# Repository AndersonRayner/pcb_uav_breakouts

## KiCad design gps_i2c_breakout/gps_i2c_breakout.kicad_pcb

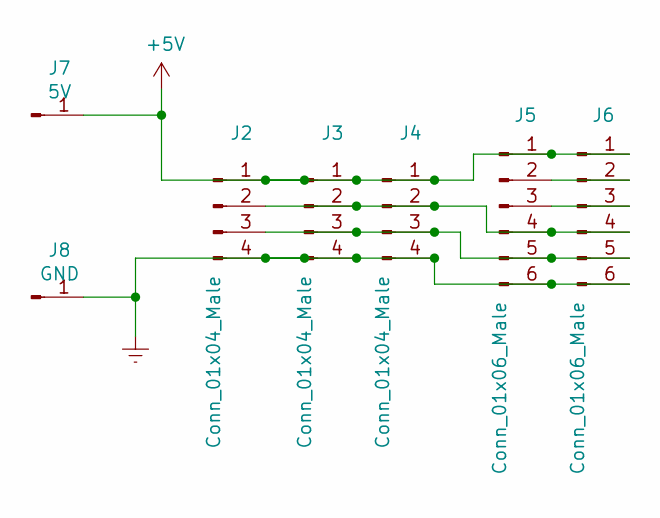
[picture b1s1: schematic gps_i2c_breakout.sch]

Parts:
J2, J3, J4: Conn_01x04_Male; JST_GH_BM04B-GHS-TBT_1x04-1MP_P1.25mm_Vertical
J5, J6: Conn_01x06_Male; JST_GH_BM06B-GHS-TBT_1x06-1MP_P1.25mm_Vertical
J7: 5V; TestPoint_Pad_2.5x2.5mm
J8: GND; TestPoint_Pad_2.5x2.5mm

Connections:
+5V: J2.1, J3.1, J4.1, J5.1, J6.1, J7.1
Earth: J2.4, J3.4, J4.4, J5.6, J6.6, J8.1
unnamed: J2.2, J3.2, J4.2, J5.4, J6.4
unnamed: J2.3, J3.3, J4.3, J5.5, J6.5
unnamed: J5.2, J6.2
unnamed: J5.3, J6.3

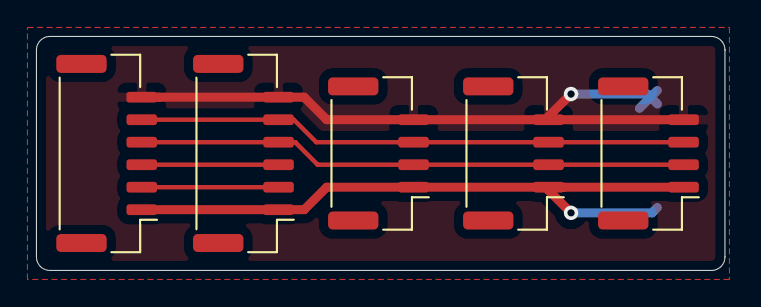
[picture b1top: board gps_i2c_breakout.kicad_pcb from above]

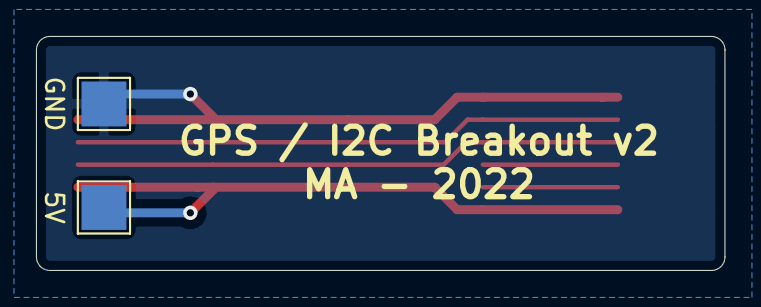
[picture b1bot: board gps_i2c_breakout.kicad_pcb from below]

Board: 2 copper layers, 38.2 x 13.0 mm, 7 parts (2 on the bottom side), 6 nets.

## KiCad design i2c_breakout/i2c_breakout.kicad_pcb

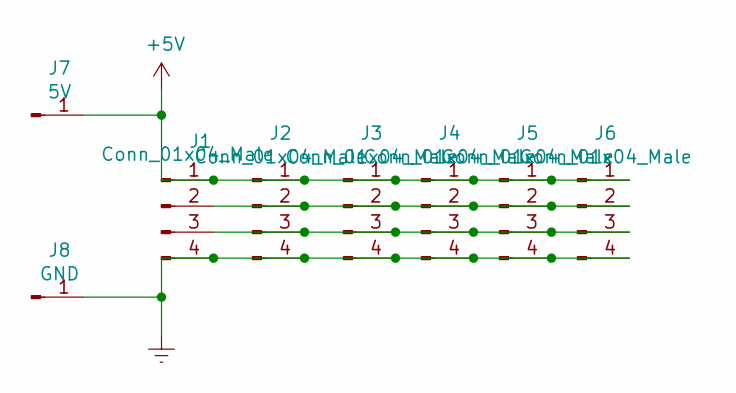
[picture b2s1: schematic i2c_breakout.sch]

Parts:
J1, J2, J3, J4, J5, J6: Conn_01x04_Male; JST_GH_BM04B-GHS-TBT_1x04-1MP_P1.25mm_Vertical
J7: 5V; TestPoint_Pad_2.5x2.5mm
J8: GND; TestPoint_Pad_2.5x2.5mm

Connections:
+5V: J1.1, J2.1, J3.1, J4.1, J5.1, J6.1, J7.1
Earth: J1.4, J2.4, J3.4, J4.4, J5.4, J6.4, J8.1
unnamed: J1.2, J2.2, J3.2, J4.2, J5.2, J6.2
unnamed: J1.3, J2.3, J3.3, J4.3, J5.3, J6.3

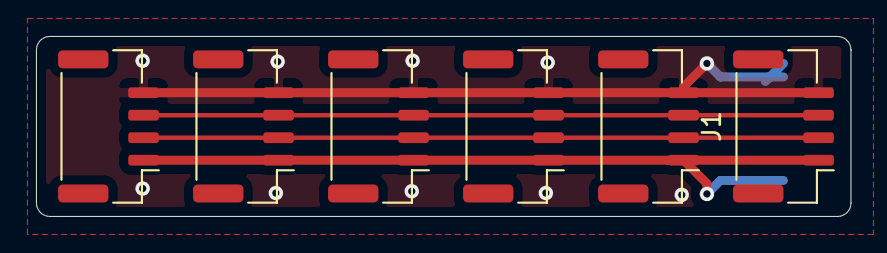
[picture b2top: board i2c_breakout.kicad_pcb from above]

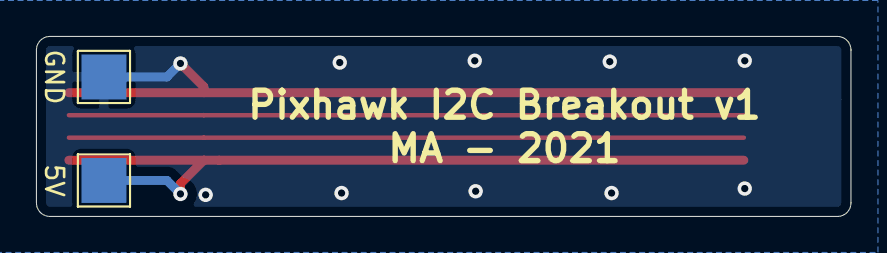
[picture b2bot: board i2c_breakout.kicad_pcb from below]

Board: 2 copper layers, 45.2 x 10.0 mm, 8 parts (2 on the bottom side), 4 nets.

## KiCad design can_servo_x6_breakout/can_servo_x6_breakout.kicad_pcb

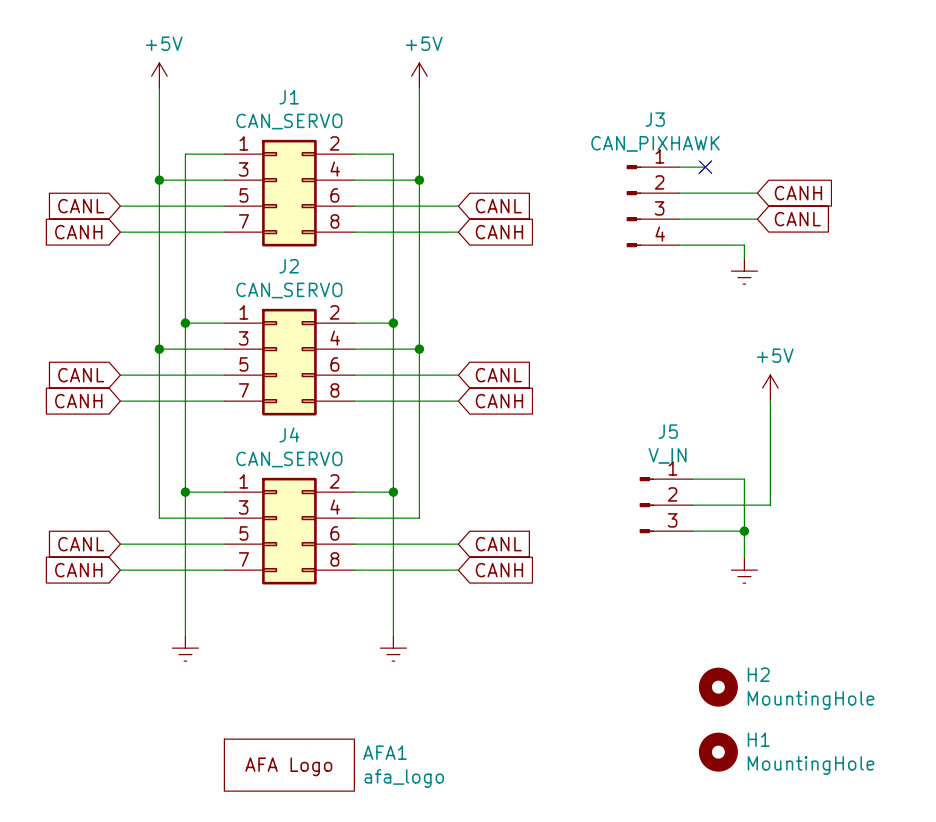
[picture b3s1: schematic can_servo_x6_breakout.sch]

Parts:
AFA1: afa_logo
H1, H2: MountingHole; MountingHole_3.2mm_M3
J1, J2, J4: CAN_SERVO; PinHeader_2x04_P2.54mm_Horizontal
J3: CAN_PIXHAWK; JST_GH_SM04B-GHS-TB_1x04-1MP_P1.25mm_Horizontal
J5: V_IN; PinHeader_1x03_P2.54mm_Horizontal

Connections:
+5V: J1.3, J1.4, J2.3, J2.4, J4.3, J4.4, J5.2
CANH: J1.7, J1.8, J2.7, J2.8, J3.2, J4.7, J4.8
CANL: J1.5, J1.6, J2.5, J2.6, J3.3, J4.5, J4.6
Earth: J1.1, J1.2, J2.1, J2.2, J3.4, J4.1, J4.2, J5.1, J5.3

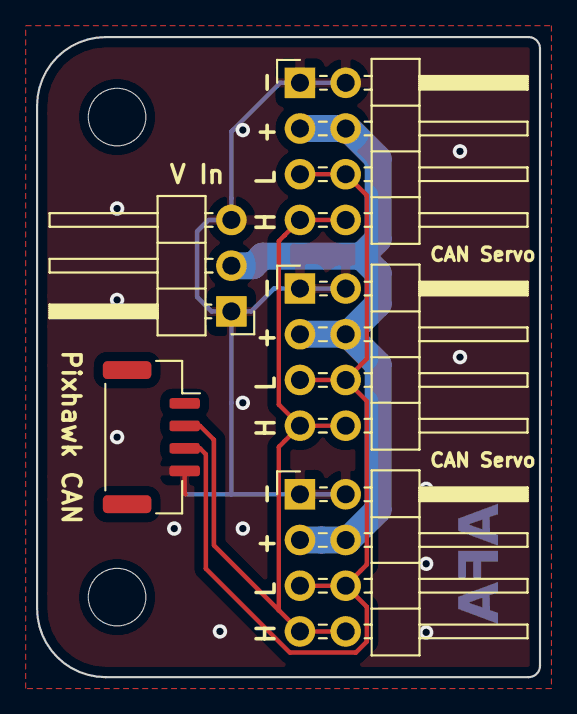
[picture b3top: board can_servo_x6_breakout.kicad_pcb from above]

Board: 2 copper layers, 27.9 x 35.6 mm, 8 parts (1 on the bottom side), 4 nets.

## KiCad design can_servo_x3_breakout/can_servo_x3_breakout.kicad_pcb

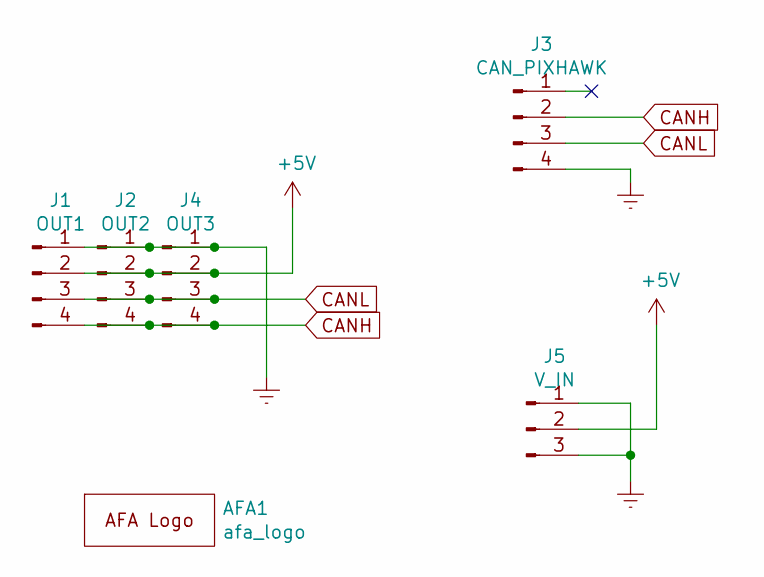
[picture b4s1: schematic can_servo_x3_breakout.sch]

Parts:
AFA1: afa_logo
J1: OUT1; PinHeader_1x04_P2.54mm_Vertical
J2: OUT2; PinHeader_1x04_P2.54mm_Vertical
J3: CAN_PIXHAWK; JST_GH_SM04B-GHS-TB_1x04-1MP_P1.25mm_Horizontal
J4: OUT3; PinHeader_1x04_P2.54mm_Horizontal
J5: V_IN; PinHeader_1x03_P2.54mm_Horizontal

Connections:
+5V: J1.2, J2.2, J4.2, J5.2
CANH: J1.4, J2.4, J3.2, J4.4
CANL: J1.3, J2.3, J3.3, J4.3
Earth: J1.1, J2.1, J3.4, J4.1, J5.1, J5.3

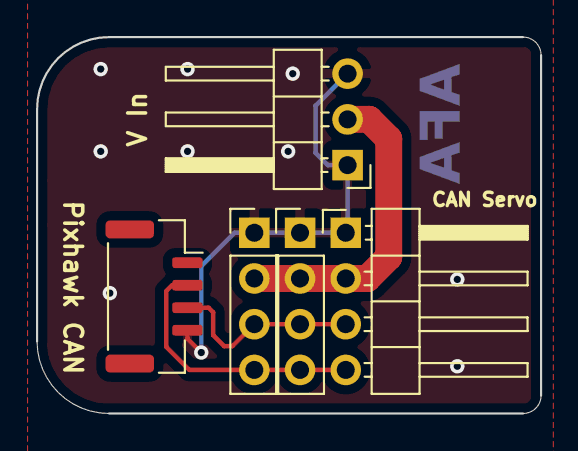
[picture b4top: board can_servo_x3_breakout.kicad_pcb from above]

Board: 2 copper layers, 28.0 x 20.9 mm, 6 parts (1 on the bottom side), 4 nets.

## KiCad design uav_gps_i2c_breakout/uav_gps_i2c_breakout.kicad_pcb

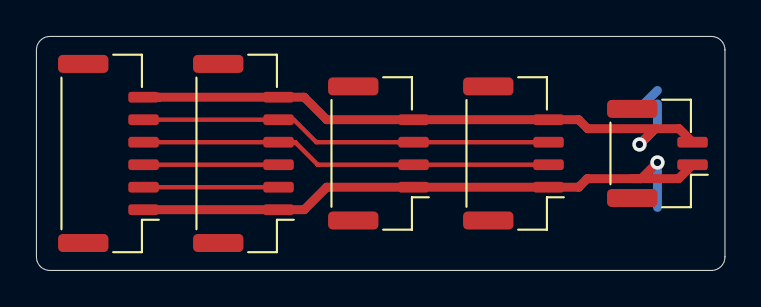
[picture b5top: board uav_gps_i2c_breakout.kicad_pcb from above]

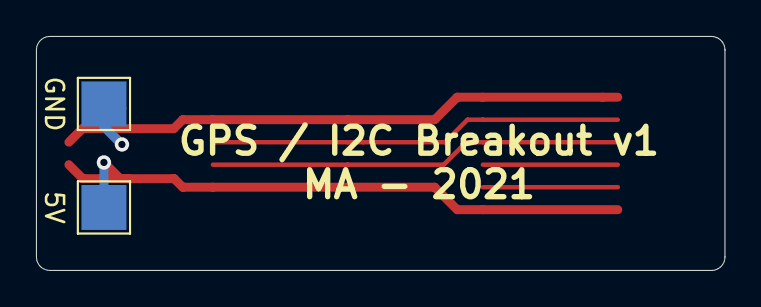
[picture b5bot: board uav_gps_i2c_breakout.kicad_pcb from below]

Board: 2 copper layers, 38.2 x 13.0 mm, 7 parts (2 on the bottom side), 6 nets.

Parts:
J1: Conn_01x02_Male; JST_GH_BM02B-GHS-TBT_1x02-1MP_P1.25mm_Vertical
J2, J3: Conn_01x04_Male; JST_GH_BM04B-GHS-TBT_1x04-1MP_P1.25mm_Vertical
J4, J5: Conn_01x04_Male; JST_GH_BM06B-GHS-TBT_1x06-1MP_P1.25mm_Vertical
J7: 5V; TestPoint_Pad_2.5x2.5mm
J8: GND; TestPoint_Pad_2.5x2.5mm

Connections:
+5V: J1.1, J2.1, J3.1, J4.1, J5.1, J7.1
Earth: J1.2, J2.4, J3.4, J4.6, J5.6, J8.1
unnamed: J2.2, J3.2, J4.4, J5.4
unnamed: J2.3, J3.3, J4.5, J5.5
unnamed: J4.2, J5.2
unnamed: J4.3, J5.3

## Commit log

2021-10-17 Added some extra boards, did some renaming
2021-12-29 Added a ground plane where it was forgotten
2021-12-29 Removing old gerbers
2022-07-05 Updated the I2C and GPS breakout boards with ground fills
